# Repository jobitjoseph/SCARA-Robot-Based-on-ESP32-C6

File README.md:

# [DIY Scara Robot Based on RISC-V Architecture](https://circuitdigest.com/videos/scara-robotic-arm-using-esp32)

<br>
A DIY SCARA (Selective Compliance Assembly Robot Arm) robot is a versatile, compact robotic arm designed for tasks requiring precision, such as assembly, sorting, and pick-and-place operations. As robotics becomes integral to modern industry and education, SCARA robots offer a practical and accessible way to explore automation, robotics programming, and motion control. This project combines affordability with high functionality, making it a valuable tool for learning and small-scale automation.
At the heart of the robot lies the ESP32-C6 WROOM module, a powerful microcontroller equipped with Wi-Fi and Bluetooth capabilities, ensuring seamless connectivity and control. The robot's motion is driven by NEMA 17 stepper motors, powered by TMC2209 drivers known for their smooth and efficient operation. Two SG90S servo motors handle the gripper, enabling precise manipulation of objects. The robot’s electronics are powered by a robust power system, featuring an LM2596-5 buck converter to step down a wide input voltage to 5V. This 5V rail is further regulated to 3.3V by an ADP7118AUJZ-3.3 low-noise CMOS LDO from Analog Devices, providing stable power to the ESP32-C6. Analog Devices’s MAX6899 supervisor IC ensures reliable boot-up of the system, while an onboard RGB LED offers visual feedback for status indications. The SCARA robot connects to a computer via a USB Type-C port, leveraging the ESP32-C6's native USB interface for streamlined communication. Control software, written in Python, provides an intuitive interface to operate the robot, featuring functions like direct control and a record-and-playback mode. This functionality allows users to program complex movements by recording and replaying actions with precision. The robot’s firmware is developed using the Arduino IDE, enabling customization and further development by hobbyists and professionals alike.

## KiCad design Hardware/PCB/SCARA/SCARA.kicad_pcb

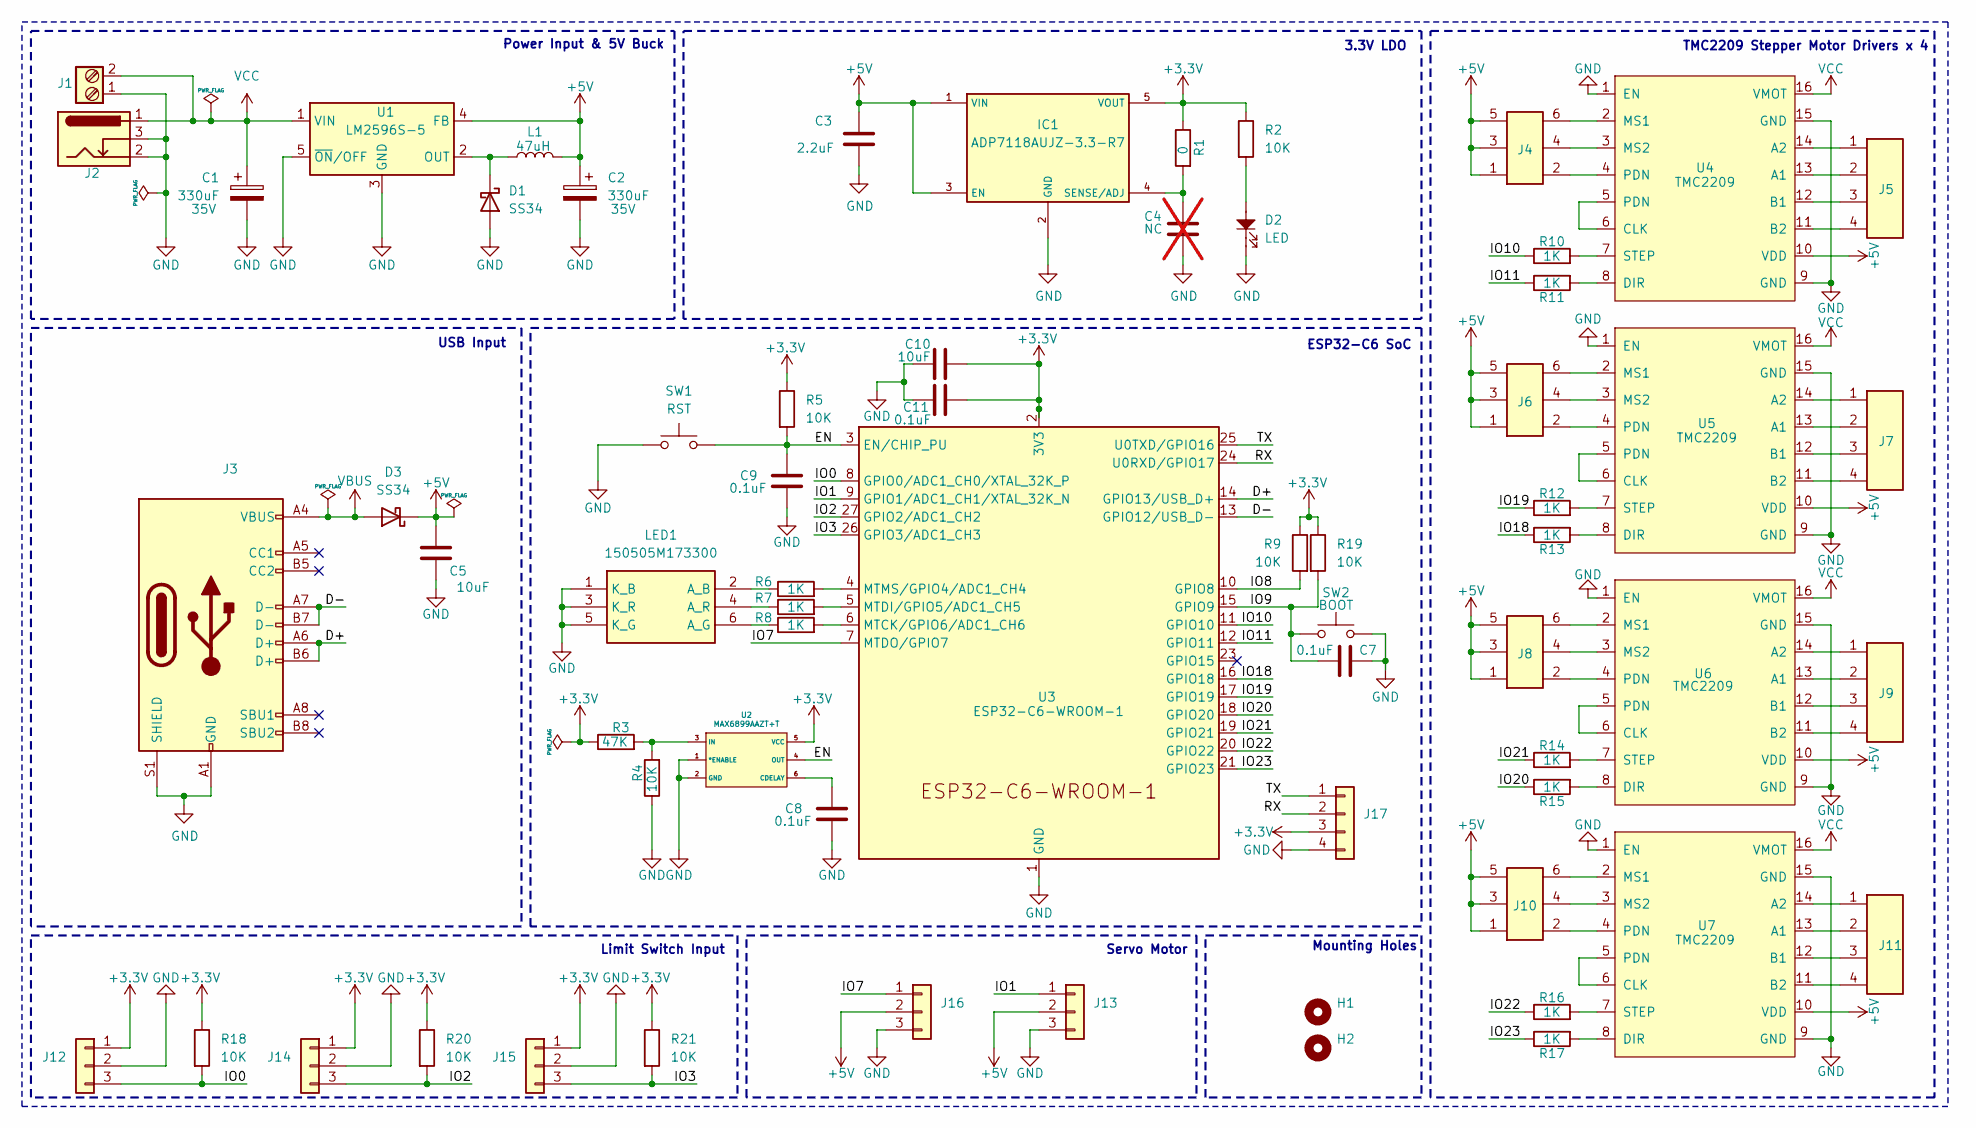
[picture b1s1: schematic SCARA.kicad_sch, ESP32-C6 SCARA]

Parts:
C1, C2: 330uF; CAP_J-V_10X10P5_RUB; Voltage 35V
C3: 2.2uF; C_0603_1608Metric
C4: NC; C_0603_1608Metric; not fitted
C5, C10: 10uF; C_0805_2012Metric
C7, C8, C9, C11: 0.1uF; C_0603_1608Metric
D1, D3: SS34; D_SMA
D2: LED; LED_0805_2012Metric
H1, H2: MountingHole; MountingHole_2.2mm_M2_Pad
IC1: ADP7118AUJZ-3.3-R7; SOT95P280X100-5N; Mouser Part Number 584-ADP7118AUJZ3.3R7
J1: Screw_Terminal_2_P5.00mm; TerminalBlock_Phoenix_PT-1,5-2-5.0-H_1x02_P5.00mm_Horizontal
J2: Barrel_Jack_Switch; BarrelJack_Kycon_KLDX-0202-xC_Horizontal
J3: USB_C_Receptacle_USB2.0; USB_C_Receptacle_HRO_TYPE-C-31-M-12
J4, J6, J8, J10: Conn_02x03_Top_Bottom; PinHeader_2x03_P2.54mm_Vertical
J5, J7, J9, J11: Conn_01x04; JST_XH_B4B-XH-AM_1x04_P2.50mm_Vertical
J12, J13, J14, J15, J16: Conn_01x03; JST_XH_B3B-XH-AM_1x03_P2.50mm_Vertical
J17: Conn_01x04; JST_EH_B4B-EH-A_1x04_P2.50mm_Vertical
L1: 47uH; L_12x12mm_H8mm
LED1: 150505M173300; Mouser Part Number 710-150505M173300
R1: 0; R_0603_1608Metric
R2, R4, R5, R9, R18, R19, R20, R21: 10K; R_0603_1608Metric
R3: 47K; R_0603_1608Metric
R6, R7, R8, R10, R11, R12, R13, R14, R15, R16, R17: 1K; R_0603_1608Metric
SW1: RST; Tactile 3x4x2mm TS-A010
SW2: BOOT; Tactile 3x4x2mm TS-A010
U1: LM2596S-5; TO-263-5_TabPin3
U2: MAX6899AAZT+T
U3: ESP32-C6-WROOM-1
U4, U5, U6, U7: TMC2209; MODULE_TMC2209_SILENTSTEPSTICK

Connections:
+3.3V: C10.1, C11.1, IC1.5 (VOUT), J12.1, J14.1, J15.1, J17.3, R1.1, R2.1, R3.1, R5.1, R9.1, R18.1, R19.1, R20.1, R21.1, U2.5 (VCC), U3.2 (3V3)
+5V: C2.1, C3.1, C5.1, D3.1 (K), IC1.1 (VIN), IC1.3 (EN), J4.1, J4.3, J4.5, J6.1, J6.3, J6.5, J8.1, J8.3, J8.5, J10.1, J10.3, J10.5, J13.2, J16.2, L1.2, U1.4 (FB), U4.10 (VDD), U5.10 (VDD), U6.10 (VDD), U7.10 (VDD)
/D+: J3.A6 (D+), J3.B6 (D+), U3.14 (GPIO13/USB_D+)
/D-: J3.A7 (D-), J3.B7 (D-), U3.13 (GPIO12/USB_D-)
/EN: C9.1, R5.2, SW1.2, U2.4 (OUT), U3.3 (EN/CHIP_PU)
/IO0: J12.3, R18.2, U3.8 (GPIO0/ADC1_CH0/XTAL_32K_P)
/IO1: J13.1, U3.9 (GPIO1/ADC1_CH1/XTAL_32K_N)
/IO2: J14.3, R20.2, U3.27 (GPIO2/ADC1_CH2)
/IO3: J15.3, R21.2, U3.26 (GPIO3/ADC1_CH3)
/IO7: J16.1, U3.7 (MTDO/GPIO7)
/IO8: R9.2, U3.10 (GPIO8)
/IO9: C7.2, R19.2, SW2.2, U3.15 (GPIO9)
/IO10: R10.1, U3.11 (GPIO10)
/IO11: R11.1, U3.12 (GPIO11)
/IO18: R13.1, U3.16 (GPIO18)
/IO19: R12.1, U3.17 (GPIO19)
/IO20: R15.1, U3.18 (GPIO20)
/IO21: R14.1, U3.19 (GPIO21)
/IO22: R16.1, U3.20 (GPIO22)
/IO23: R17.1, U3.21 (GPIO23)
/RX: J17.2, U3.24 (U0RXD/GPIO17)
/TX: J17.1, U3.25 (U0TXD/GPIO16)
GND: C1.2, C2.2, C3.2, C4.2, C5.2, C7.1, C8.2, C9.2, C10.2, C11.2, D1.2 (A), D2.1, IC1.2 (GND), J1.1, J2.2, J2.3, J3.A1 (GND), J3.A12 (GND), J3.B1 (GND), J3.B12 (GND), J3.S1 (SHIELD), J12.2, J13.3, J14.2, J15.2, J16.3, J17.4, LED1.1 (K_B), LED1.3 (K_R), LED1.5 (K_G), R4.1, SW1.1, SW2.1, U1.3 (GND), U1.5 (~ON/OFF), U2.1 (*ENABLE), U2.2 (GND), U3.1 (GND), U3.28 (GND), U3.29 (GND), U4.1 (EN), U4.9 (GND), U4.15 (GND), U5.1 (EN), U5.9 (GND), U5.15 (GND), U6.1 (EN), U6.9 (GND), U6.15 (GND), U7.1 (EN), U7.9 (GND), U7.15 (GND)
unnamed: D1.1 (K), L1.1, U1.2 (OUT)
unnamed: D2.2, R2.2
unnamed: C4.1, IC1.4 (SENSE/ADJ), R1.2
unnamed: J4.2, U4.4 (PDN)
unnamed: J4.4, U4.3 (MS2)
unnamed: J4.6, U4.2 (MS1)
unnamed: J5.1, U4.14 (A2)
unnamed: J5.2, U4.13 (A1)
unnamed: J5.3, U4.12 (B1)
unnamed: J5.4, U4.11 (B2)
unnamed: J6.2, U5.4 (PDN)
unnamed: J6.4, U5.3 (MS2)
unnamed: J6.6, U5.2 (MS1)
unnamed: J7.1, U5.14 (A2)
unnamed: J7.2, U5.13 (A1)
unnamed: J7.3, U5.12 (B1)
unnamed: J7.4, U5.11 (B2)
unnamed: J8.2, U6.4 (PDN)
unnamed: J8.4, U6.3 (MS2)
unnamed: J8.6, U6.2 (MS1)
unnamed: J9.1, U6.14 (A2)
unnamed: J9.2, U6.13 (A1)
unnamed: J9.3, U6.12 (B1)
unnamed: J9.4, U6.11 (B2)
unnamed: J10.2, U7.4 (PDN)
unnamed: J10.4, U7.3 (MS2)
unnamed: J10.6, U7.2 (MS1)
unnamed: J11.1, U7.14 (A2)
unnamed: J11.2, U7.13 (A1)
unnamed: J11.3, U7.12 (B1)
unnamed: J11.4, U7.11 (B2)
unnamed: LED1.2 (A_B), R6.1
unnamed: LED1.6 (A_G), R8.1
unnamed: LED1.4 (A_R), R7.1
unnamed: C8.1, U2.6 (CDELAY)
unnamed: R3.2, R4.2, U2.3 (IN)
unnamed: R8.2, U3.6 (MTCK/GPIO6/ADC1_CH6)
unnamed: R7.2, U3.5 (MTDI/GPIO5/ADC1_CH5)
unnamed: R6.2, U3.4 (MTMS/GPIO4/ADC1_CH4)
unnamed: U4.5 (PDN), U4.6 (CLK)
unnamed: R11.2, U4.8 (DIR)
unnamed: R10.2, U4.7 (STEP)
unnamed: U5.5 (PDN), U5.6 (CLK)
unnamed: R13.2, U5.8 (DIR)
unnamed: R12.2, U5.7 (STEP)
unnamed: U6.5 (PDN), U6.6 (CLK)
unnamed: R15.2, U6.8 (DIR)
unnamed: R14.2, U6.7 (STEP)
unnamed: U7.5 (PDN), U7.6 (CLK)
unnamed: R17.2, U7.8 (DIR)
unnamed: R16.2, U7.7 (STEP)
VBUS: D3.2 (A), J3.A4 (VBUS), J3.A9 (VBUS), J3.B4 (VBUS), J3.B9 (VBUS)
VCC: C1.1, J1.2, J2.1, U1.1 (VIN), U4.16 (VMOT), U5.16 (VMOT), U6.16 (VMOT), U7.16 (VMOT)

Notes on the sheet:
TMC2209 Stepper Motor Drivers x 4
Power Input & 5V Buck
ESP32-C6 SoC
Servo Motor
3.3V LDO
USB Input
Limit Switch Input
Mounting Holes

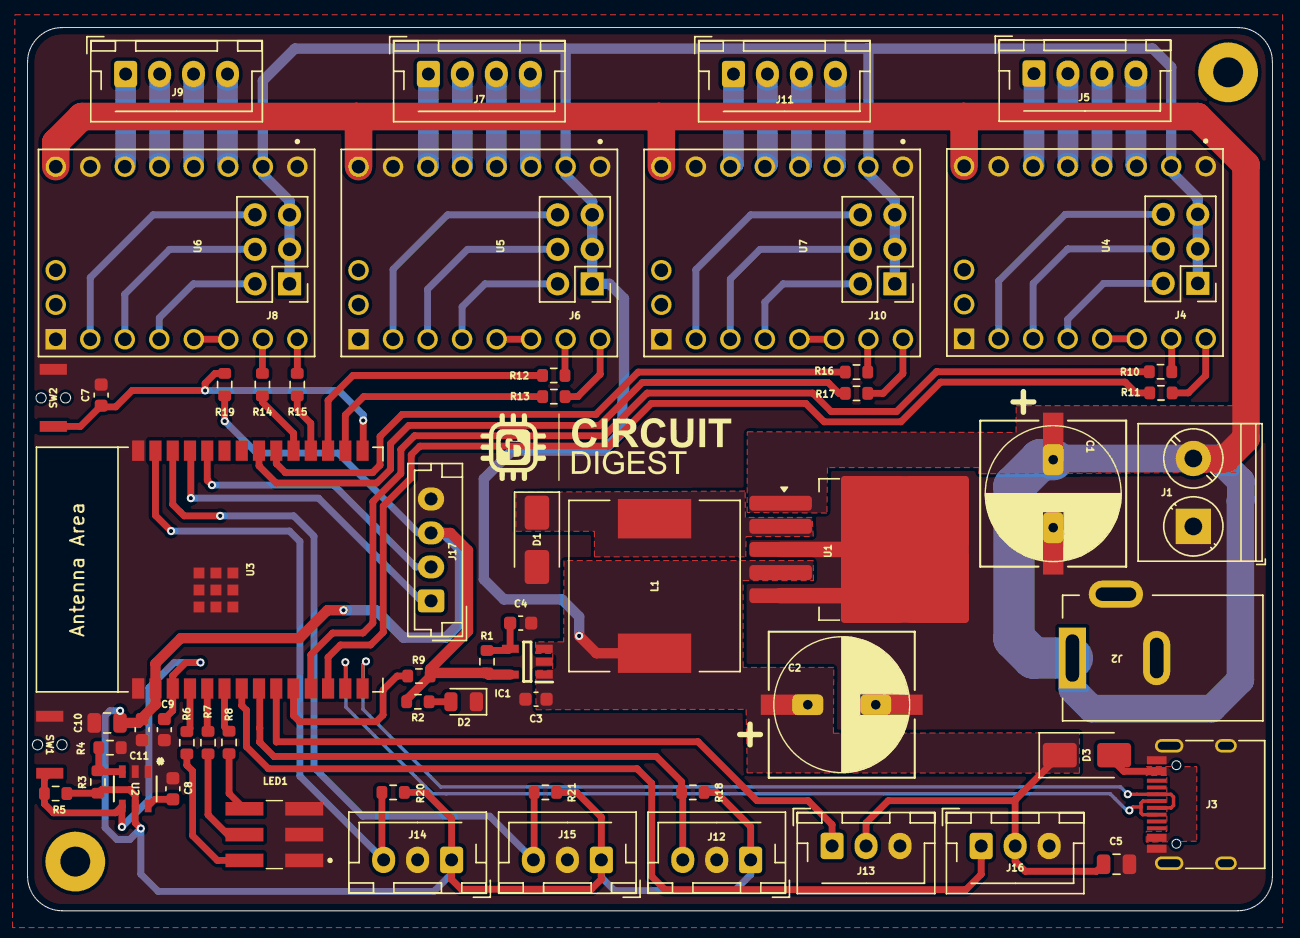
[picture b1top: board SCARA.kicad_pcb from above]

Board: 2 copper layers, 91.6 x 65.0 mm, 65 parts (0 on the bottom side), 76 nets.

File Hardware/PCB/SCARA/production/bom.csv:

Designator,Footprint,Quantity,Value,LCSC Part #
"C1, C2",CAP_J-V_10X10P5_RUB,2,330uF,
"C10, C5",0805,2,10uF,
"C11, C7, C8, C9",0603,4,0.1uF,
C3,0603,1,2.2uF,
C4,0603,1,NC,
"D1, D3",D_SMA,2,SS34,
D2,0805,1,LED,
IC1,SOT95P280X100-5N,1,ADP7118AUJZ-3.3-R7,
J1,"TerminalBlock_Phoenix_PT-1,5-2-5.0-H_1x02_P5.00mm_Horizontal",1,Screw_Terminal_2_P5.00mm,
"J10, J4, J6, J8",PinHeader_2x03_P2.54mm_Vertical,4,Conn_02x03_Top_Bottom,
"J11, J5, J7, J9",JST_XH_B4B-XH-AM_1x04_P2.50mm_Vertical,4,Conn_01x04,
"J12, J13, J14, J15, J16",JST_XH_B3B-XH-AM_1x03_P2.50mm_Vertical,5,Conn_01x03,
J17,JST_EH_B4B-EH-A_1x04_P2.50mm_Vertical,1,Conn_01x04,
J2,BarrelJack_Kycon_KLDX-0202-xC_Horizontal,1,Barrel_Jack_Switch,
J3,USB_C_Receptacle_HRO_TYPE-C-31-M-12,1,USB_C_Receptacle_USB2.0,
L1,L_12x12mm_H8mm,1,47uH,
LED1,150505M173300,1,150505M173300,
R1,0603,1,0,
"R10, R11, R12, R13, R14, R15, R16, R17, R6, R7, R8",0603,11,1K,
"R18, R19, R2, R20, R21, R4, R5, R9",0603,8,10K,
R3,0603,1,47K,
SW1,Tactile 3x4x2mm TS-A010,1,RST,
SW2,Tactile 3x4x2mm TS-A010,1,BOOT,
U1,TO-263-5_TabPin3,1,LM2596S-5,
U2,MAX6899AAZT+T,1,MAX6899AAZT+T,
U3,ESP32-C6-WROOM-1,1,ESP32-C6-WROOM-1,
"U4, U5, U6, U7",MODULE_TMC2209_SILENTSTEPSTICK,4,TMC2209_SILENTSTEPSTICK,
